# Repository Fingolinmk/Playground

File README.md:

# Playground
This repository gathers all Material used to create a "smart lamp" that can be controlled via MQTT plus a controller board, that can send MQTT messages.
Find more here: https://fingolinmk.github.io/Playground/

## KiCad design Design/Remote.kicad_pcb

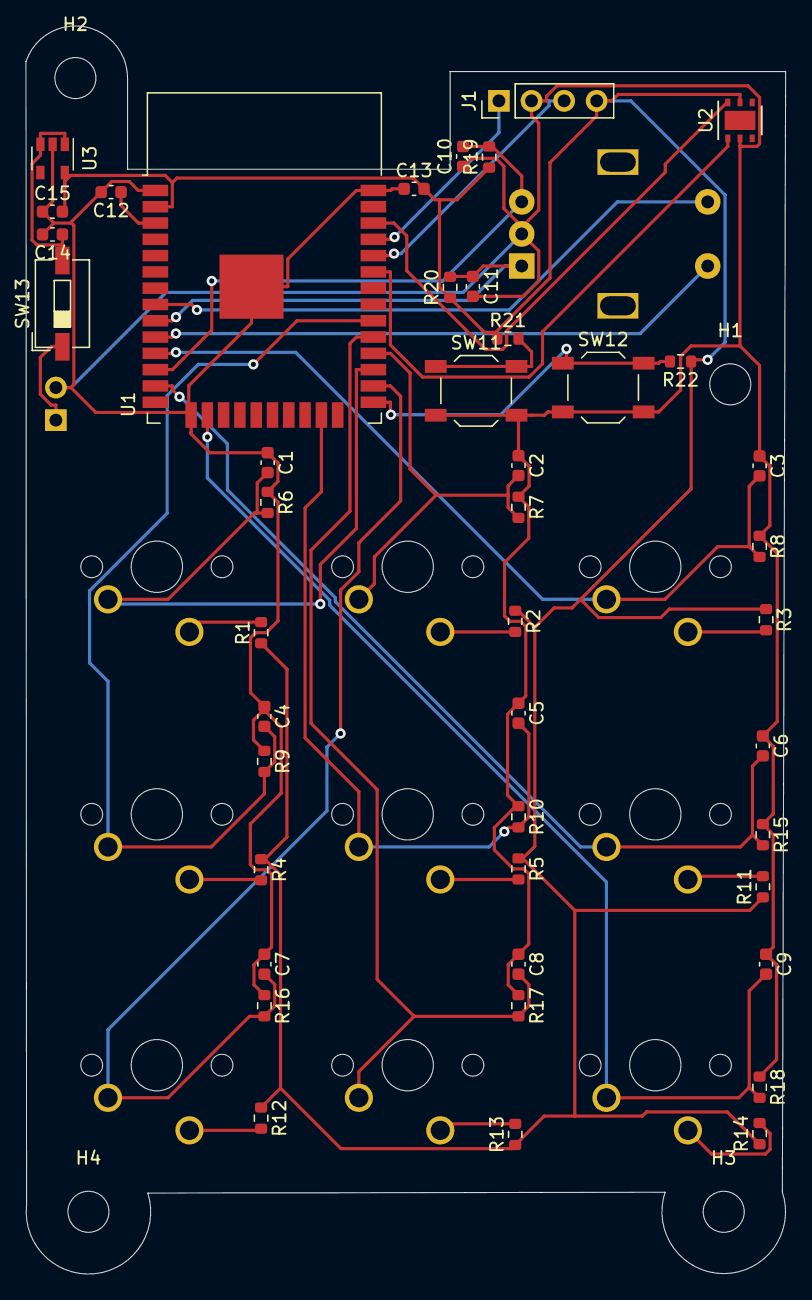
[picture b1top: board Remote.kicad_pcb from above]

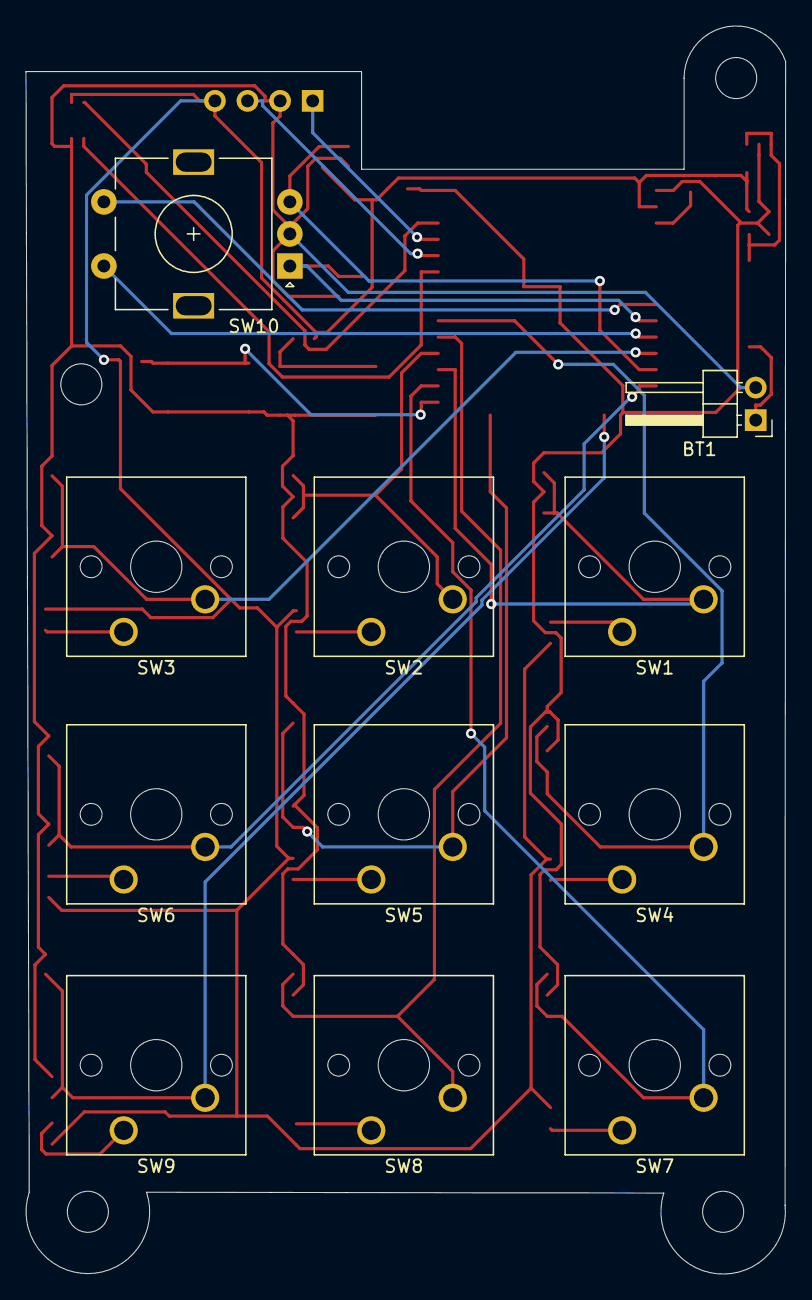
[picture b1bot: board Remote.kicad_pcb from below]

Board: 2 copper layers, 59.2 x 97.3 mm, 59 parts (11 on the bottom side), 33 nets.

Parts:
BT1: Battery; PinHeader_1x02_P2.54mm_Horizontal
C1, C2, C3, C4, C5, C6, C7, C8, C9, C10, C11, C12, C13: 100nF; C_0603_1608Metric
C14, C15: 1uF; C_0603_1608Metric
H1, H2, H3, H4: MountingHole; MountingHole_3.2mm_M3
J1: Conn_01x04_Female; PinHeader_1x04_P2.54mm_Vertical
R1, R2, R3, R4, R5, R11, R12, R13, R14, R19, R20, R21, R22: 10kR; R_0603_1608Metric
R6, R7, R8, R9, R10, R15, R16, R17, R18: 100R; R_0603_1608Metric
SW1, SW2, SW3, SW4, SW5, SW6, SW7, SW8, SW9: SW_Push; SW_Cherry_MX_1.00u_PCB
SW10: Rotary_Encoder_Switch; RotaryEncoder_Alps_EC11E-Switch_Vertical_H20mm
SW11: SW_Reset; SW_SPST_TL3342
SW12: SW_BOOTMODE; SW_SPST_TL3342
SW13: SW_DIP_x01; SW_DIP_SPSTx01_Slide_6.7x4.1mm_W6.73mm_P2.54mm_LowProfile_J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
U1: ESP32-WROOM-32D; ESP32-WROOM-32
U2: HDC1080; Texas_PWSON-N6
U3: AP2112K-3.3; SOT-23-5

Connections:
/RX: J1.3, U1.34
/TX: J1.1, U1.35
BOOTMODE: R22.2, SW12.1, U1.25
ENABLE: C12.1, U1.3
GND: BT1.2, C1.1, C2.1, C3.1, C4.1, C5.1, C6.1, C7.1, C8.1, C9.1, C10.1, C11.2, C12.2, C13.1, C14.2, C15.1, J1.2, R6.1, R7.1, R8.1, R9.1, R10.1, R15.1, R16.1, R17.1, R18.1, SW10.C, SW11.2, SW12.2, U1.1, U1.15, U1.38, U1.39, U2.2, U3.2
GPIO4: C7.2, R16.2, SW7.2, U1.26
GPIO5: C8.2, R17.2, SW8.2, U1.29
GPIO13: C9.2, R18.2, SW9.2, U1.16
GPIO14: C6.2, R15.2, SW6.2, U1.13
GPIO15: C5.2, R10.2, SW5.2, U1.23
GPIO16: C1.2, R6.2, SW1.2, U1.27
GPIO17: C2.2, R7.2, SW2.2, U1.28
GPIO18: C4.2, R9.2, SW4.2, U1.30
GPIO25: SW10.S2, U1.10
GPIO26: C3.2, R8.2, SW3.2, U1.11
GPIO27: C10.2, R19.2, SW10.B, U1.12
GPIO32: SW10.S1, U1.8
GPIO33: C11.1, R20.2, SW10.A, U1.9
unnamed: BT1.1, SW13.1
unnamed: C14.1, SW13.2, U3.1, U3.3
unnamed: R1.2, SW1.1
unnamed: R2.2, SW2.1
unnamed: R3.2, SW3.1
unnamed: R4.2, SW4.1
unnamed: R5.2, SW5.1
unnamed: R11.2, SW6.1
unnamed: R12.2, SW7.1
unnamed: R13.2, SW8.1
unnamed: R14.2, SW9.1
unnamed: R21.2, SW11.1
VCC: C13.2, C15.2, J1.4, R1.1, R2.1, R3.1, R4.1, R5.1, R11.1, R12.1, R13.1, R14.1, R19.1, R20.1, R21.1, R22.1, U1.2, U2.5, U3.5
scl: U1.36, U2.6
sda: U1.33, U2.1

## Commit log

2022-02-02 Added description of mqtt commands
2022-02-02 Added slideshow
2022-02-02 minor changes, end of lunchbreak
2022-02-03 Docs to /docs
2022-02-03 Some spelling errors
2022-02-03 compressed images
2022-02-03 Formatting
2022-02-03 Added a license
2022-02-03 More Styling
2022-02-03 Added vendor file
2022-02-07 Lunchbreak over
2022-02-07 fix: prism syntax highlighting for dynamically loaded js
2022-02-07 Changed my wifi PW :D
2022-02-07 Removed secrets
2022-02-07 Added tabs
2022-02-07 removed some unnecessary logs
2022-02-07 A bit more styling
2022-02-07 formatting error
2022-04-02 now with tests
2022-04-02 More tests
2022-04-02 refactored toggle
2022-06-02 Minor decoupling from Arduino in colormatrix_helper.h
2022-06-02 Minor refactoring
2022-06-02 minor adaption
2022-07-10 testing new page
2022-07-10 Another try
2022-07-10 Another one
2022-07-10 now?
2022-07-10 Trying to fix images
2022-08-25 Updated some node dependencies, and added the CAD file of the lampshade
2022-08-25 renamed all the folders
2022-08-25 minor changes
2022-08-25 updated build
2022-08-26 Adopted filepaths
2022-08-29 Minor Fix
2022-08-29 added flutter gititnore
2022-08-29 added the flutter app
2022-08-29 minor tweakes
2022-10-01 Updated the react page
2022-10-01 Added images
2022-10-01 added a second carousel
2022-10-01 new build for doc
2022-10-01 Fixed a minor mistake
2022-10-01 Sider is now responsive
2022-10-01 build
2022-10-01 Fixed images
2022-10-01 Added the image in depl
2022-10-01 ok there are 3 folders for images now..
2022-10-01 in principle now adaptive
